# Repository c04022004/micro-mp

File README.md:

# Multi-purpose Arduino Micro shield

This is an attempt stuff functionalities onto an ATmega32U4-based board while keeping a moderate footprint and simple low-cost parts. The original version is made out of the necessity to replace dupont(jumper) wires for stability. The board gradually expanded into the current form. This is also my first few PCBs, so expect it to be less than optimal. I learnt a lot going through the design, soldering, debug process and enjoyed working on it.

## Functionalities/Devices
- 0.96'/1.3' OLED monitor
- RS485 thru MAX485
- Dual USB Serial (Native+CP2102)
- WS2812 LED, expandable, physical off SW
- EEPROM (ATMEL AT24C )
- PCF8574 I/O expansion (8 Pins)
- Type-C USB Power, fuse
- Buttons, Reset button
- IDC header (2x05) for external boards

## Renderings

## Actual Hardware
Evolving Hardware:  

## Library Used
- https://github.com/keebio/keebio-components
- https://github.com/keebio/Keebio-Parts.pretty
- https://github.com/sparkfun/SparkFun-KiCad-Libraries
- https://github.com/Digi-Key/digikey-kicad-library

## To be constructed
- BOM
- Demo Images
- Extensions

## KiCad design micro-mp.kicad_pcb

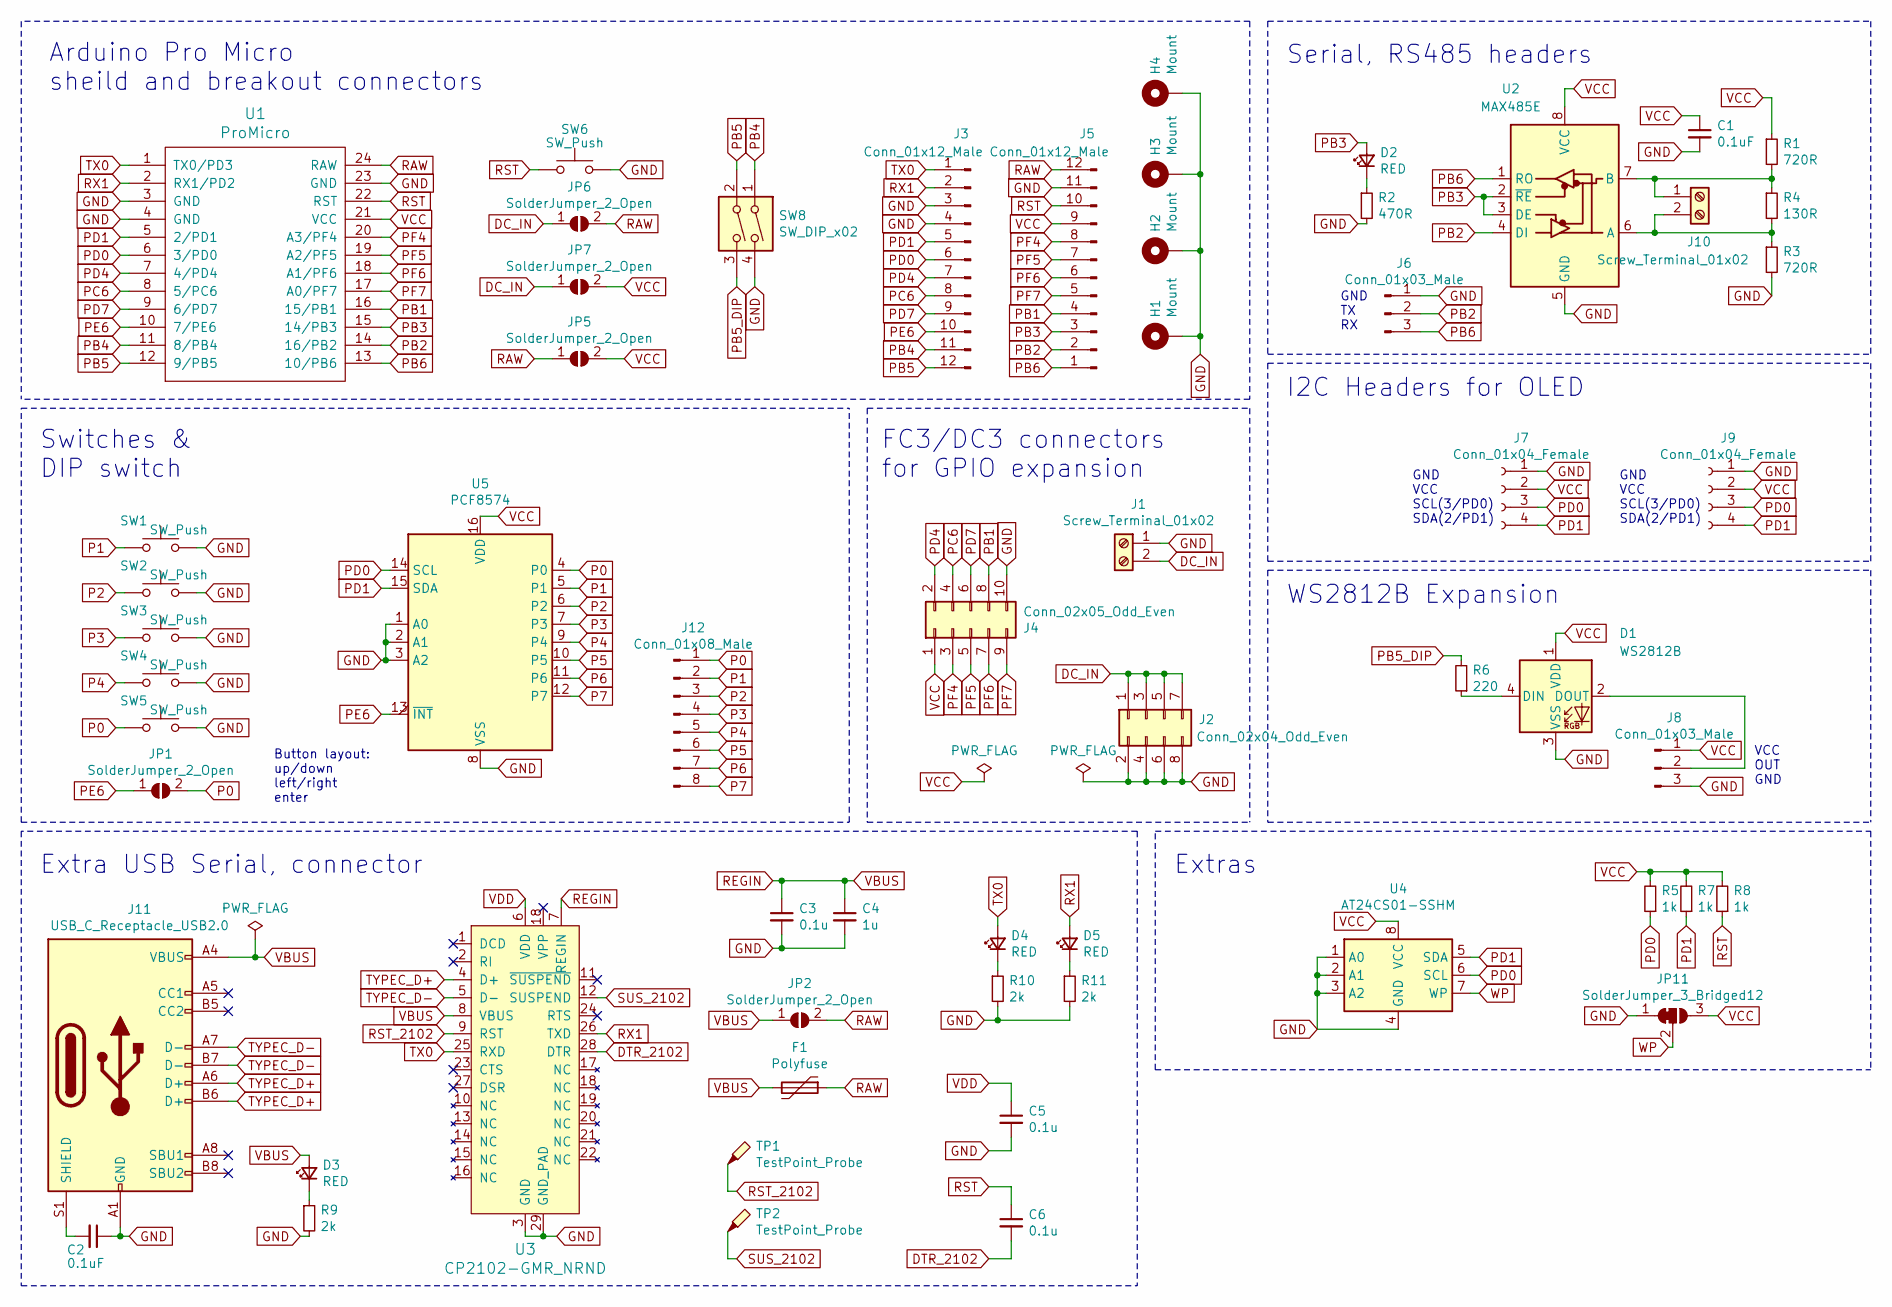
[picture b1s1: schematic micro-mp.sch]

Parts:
C1, C2: 0.1uF; C_0805_2012Metric_Pad1.15x1.40mm_HandSolder
C3, C5, C6: 0.1u; C_0805_2012Metric_Pad1.15x1.40mm_HandSolder
C4: 1u; C_0805_2012Metric_Pad1.15x1.40mm_HandSolder
D1: WS2812B; LED_WS2812B_PLCC4_5.0x5.0mm_P3.2mm
D2, D3, D4, D5: RED; D_0805_2012Metric_Pad1.15x1.40mm_HandSolder
F1: Polyfuse; Fuse_0805_2012Metric_Pad1.15x1.40mm_HandSolder
H1, H2, H3, H4: Mount; MountingHole_3.2mm_M3_Pad
J1, J10: Screw_Terminal_01x02; TerminalBlock_bornier-2_P5.08mm
J2: Conn_02x04_Odd_Even; PinHeader_2x04_P2.54mm_Vertical
J3, J5: Conn_01x12_Male; PinHeader_1x12_P2.54mm_Vertical
J4: Conn_02x05_Odd_Even; IDC-Header_2x05_P2.54mm_Vertical
J6, J8: Conn_01x03_Male; PinHeader_1x03_P2.54mm_Vertical
J7, J9: Conn_01x04_Female; PinSocket_1x04_P2.54mm_Vertical
J11: USB_C_Receptacle_USB2.0; USB_C_Receptacle_Palconn_UTC16-G
J12: Conn_01x08_Male; PinHeader_1x08_P2.54mm_Vertical
JP1, JP2, JP5, JP6, JP7: SolderJumper_2_Open; SolderJumper-2_P1.3mm_Open_Pad1.0x1.5mm
JP11: SolderJumper_3_Bridged12; SolderJumper-3_P1.3mm_Bridged12_Pad1.0x1.5mm
R1, R3: 720R; R_0805_2012Metric_Pad1.15x1.40mm_HandSolder
R2: 470R; R_0805_2012Metric_Pad1.15x1.40mm_HandSolder
R4: 130R; R_0805_2012Metric_Pad1.15x1.40mm_HandSolder
R5, R7, R8: 1k; R_0805_2012Metric_Pad1.15x1.40mm_HandSolder
R6: 220; R_0805_2012Metric_Pad1.15x1.40mm_HandSolder
R9, R10, R11: 2k; R_0805_2012Metric_Pad1.15x1.40mm_HandSolder
SW1, SW2, SW3, SW4, SW5, SW6: SW_Push; TACTILE_SWITCH_SMD_6.0X3.5MM
SW8: SW_DIP_x02; SW_DIP_SPSTx02_Slide_9.78x7.26mm_W7.62mm_P2.54mm
TP1, TP2: TestPoint_Probe; TestPoint_Pad_1.0x1.0mm
U1: ProMicro; ArduinoProMicro
U2: MAX485E; DIP-8_W7.62mm
U3: CP2102-GMR_NRND; VFQFN-28-1EP_5x5mm; MPN CP2102-GMR; Digi-Key_PN 336-1160-1-ND
U4: AT24CS01-SSHM; SOIC-8_3.9x4.9mm_P1.27mm
U5: PCF8574; SO-16_5.3x10.2mm_P1.27mm

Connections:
DC_IN: J1.2, J2.1, J2.3, J2.5, J2.7, JP6.1 (A), JP7.1 (A)
DTR_2102: C6.2, U3.28 (DTR)
GND: C1.2, C2.1, C3.2, C4.2, C5.2, D1.3 (VSS), H1.1, H2.1, H3.1, H4.1, J1.1, J2.2, J2.4, J2.6, J2.8, J3.3, J3.4, J4.10, J5.11, J6.1, J7.1, J8.3, J9.1, J11.A1 (GND), J11.A12 (GND), J11.B1 (GND), J11.B12 (GND), JP11.1 (A), R2.2, R3.2, R9.2, R10.2, R11.2, SW1.2, SW2.2, SW3.2, SW4.2, SW5.2, SW6.2, SW8.4, U1.3 (GND), U1.4 (GND), U1.23 (GND), U2.5 (GND), U3.3 (GND), U3.29 (GND_PAD), U4.1 (A0), U4.2 (A1), U4.3 (A2), U4.4 (GND), U5.1 (A0), U5.2 (A1), U5.3 (A2), U5.8 (VSS)
unnamed: C2.2, J11.S1 (SHIELD)
unnamed: D1.2 (DOUT), J8.2
unnamed: D1.4 (DIN), R6.1
unnamed: D2.1 (K), R2.1
unnamed: D3.1 (K), R9.1
unnamed: D4.1 (K), R10.1
unnamed: D5.1 (K), R11.1
unnamed: J10.1, R1.2, R4.1, U2.7 (B)
unnamed: J10.2, R3.1, R4.2, U2.6 (A)
P0: J12.1, JP1.2 (B), SW5.1, U5.4 (P0)
P1: J12.2, SW1.1, U5.5 (P1)
P2: J12.3, SW2.1, U5.6 (P2)
P3: J12.4, SW3.1, U5.7 (P3)
P4: J12.5, SW4.1, U5.9 (P4)
P5: J12.6, U5.10 (P5)
P6: J12.7, U5.11 (P6)
P7: J12.8, U5.12 (P7)
PB1: J4.8, J5.4, U1.16 (15/PB1)
PB2: J5.2, J6.2, U1.14 (16/PB2), U2.4 (DI)
PB3: D2.2 (A), J5.3, U1.15 (14/PB3), U2.2 (~RE), U2.3 (DE)
PB4: J3.11, SW8.1, U1.11 (8/PB4)
PB5: J3.12, SW8.2, U1.12 (9/PB5)
PB5_DIP: R6.2, SW8.3
PB6: J5.1, J6.3, U1.13 (10/PB6), U2.1 (RO)
PC6: J3.8, J4.4, U1.8 (5/PC6)
PD0: J3.6, J7.3, J9.3, R5.1, U1.6 (3/PD0), U4.6 (SCL), U5.14 (SCL)
PD1: J3.5, J7.4, J9.4, R7.1, U1.5 (2/PD1), U4.5 (SDA), U5.15 (SDA)
PD4: J3.7, J4.2, U1.7 (4/PD4)
PD7: J3.9, J4.6, U1.9 (6/PD7)
PE6: J3.10, JP1.1 (A), U1.10 (7/PE6), U5.13 (~INT~)
PF4: J4.3, J5.8, U1.20 (A3/PF4)
PF5: J4.5, J5.7, U1.19 (A2/PF5)
PF6: J4.7, J5.6, U1.18 (A1/PF6)
PF7: J4.9, J5.5, U1.17 (A0/PF7)
RAW: F1.1, J5.12, JP2.2 (B), JP5.1 (A), JP6.2 (B), U1.24 (RAW)
REGIN: C3.1, C4.1, D3.2 (A), F1.2, J11.A4 (VBUS), J11.A9 (VBUS), J11.B4 (VBUS), J11.B9 (VBUS), JP2.1 (A), U3.7 (REGIN), U3.8 (VBUS)
RST: C6.1, J5.10, R8.1, SW6.1, U1.22 (RST)
RST_2102: TP1.1, U3.9 (RST)
RX1: D5.2 (A), J3.2, U1.2 (RX1/PD2), U3.26 (TXD)
SUS_2102: TP2.1, U3.12 (SUSPEND)
TX0: D4.2 (A), J3.1, U1.1 (TX0/PD3), U3.25 (RXD)
TYPEC_D+: J11.A6 (D+), J11.B6 (D+), U3.4 (D+)
TYPEC_D-: J11.A7 (D-), J11.B7 (D-), U3.5 (D-)
VCC: C1.1, D1.1 (VDD), J4.1, J5.9, J7.2, J8.1, J9.2, JP5.2 (B), JP7.2 (B), JP11.3 (B), R1.1, R5.2, R7.2, R8.2, U1.21 (VCC), U2.8 (VCC), U4.8 (VCC), U5.16 (VDD)
VDD: C5.1, U3.6 (VDD)
WP: JP11.2 (C), U4.7 (WP)

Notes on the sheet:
GND TX RX
GND VCC SCL(3/PD0) SDA(2/PD1)
Button layout: up/down left/right enter
Serial, RS485 headers
I2C Headers for OLED
Extra USB Serial, connector
VCC OUT GND
WS2812B Expansion
Switches & DIP switch
Arduino Pro Micro sheild and breakout connectors
FC3/DC3 connectors for GPIO expansion
Extras

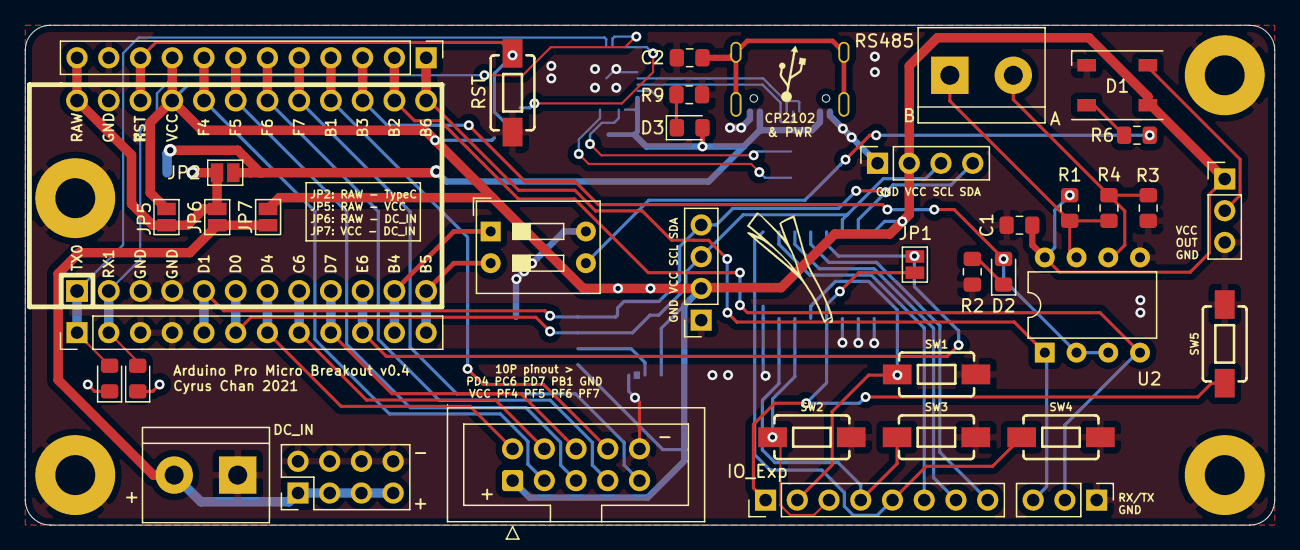
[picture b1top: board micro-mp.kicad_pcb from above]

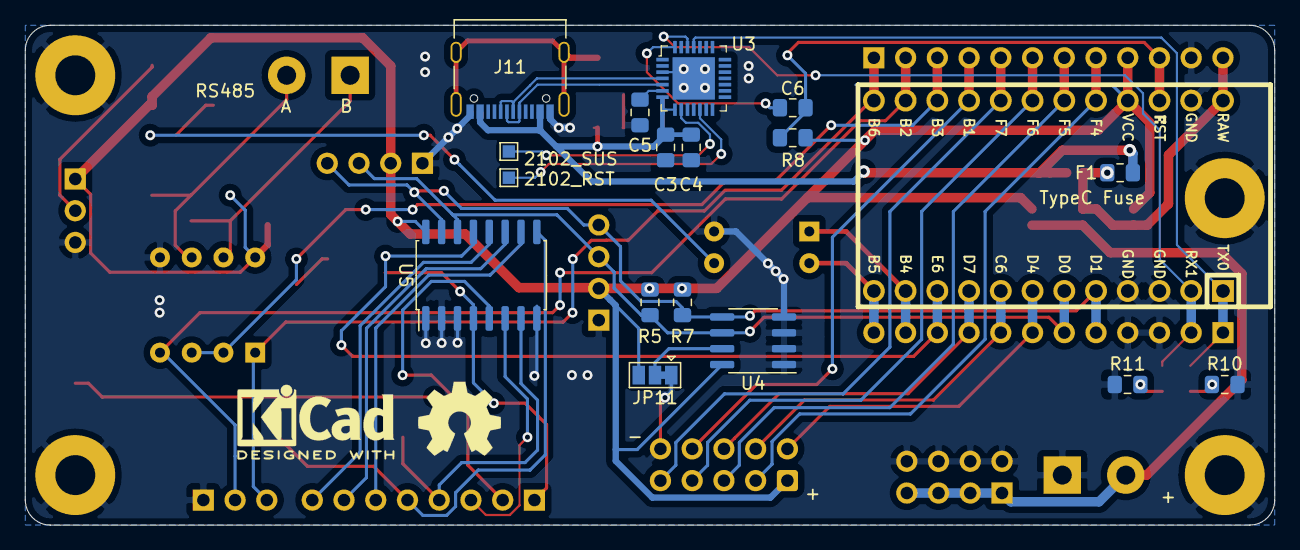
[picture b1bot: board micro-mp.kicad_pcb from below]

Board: 2 copper layers, 100.0 x 40.0 mm, 59 parts (17 on the bottom side), 49 nets.

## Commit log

2021-01-13 Inital Commit (v0.4.1)
2021-01-13 <docs> Update README.md
    - Uploading more images (actual HW)
    - Adding links to library resources
